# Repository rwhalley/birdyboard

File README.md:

# BirdyBoard 🦜

## What is BirdyBoard?

BirdyBoard is an open source Stepper Motor Controller Board powered by the Raspberry Pi Pico. BirdyBoard enables low-level control of stepper motors via the TMC2209 motor driver, making it possible to control the absolute position of gantry components without End Stop Switches. 

Create custom PCB modifications for creative projects with BirdyBoard.

## Creating Accessibility Despite Chip Shortages

BirdyBoard uses the RP2040 chip which is readily available even though the chip shortage (as of 2022) has rendered other chip options unavailable. The BirdyBoard allows for direct placement of the Pi Pico breakout board and TMC2209 breakout boards giving the reliability of a PCB without the need for complex or tedious soldering procedures for assembly.

## Link To Build of Materials + PCB Trace Tool Spreadsheets

https://docs.google.com/spreadsheets/d/1NhMLRXCss38mAH5ybtot6I5Q5R5pm-g04sVmaoJh7os/edit?usp=sharing

## Link to Pi Pico KiCad Layout Files

KiCad board layouts for the Raspberry Pi Pico are available here: https://github.com/ncarandini/KiCad-RP-Pico

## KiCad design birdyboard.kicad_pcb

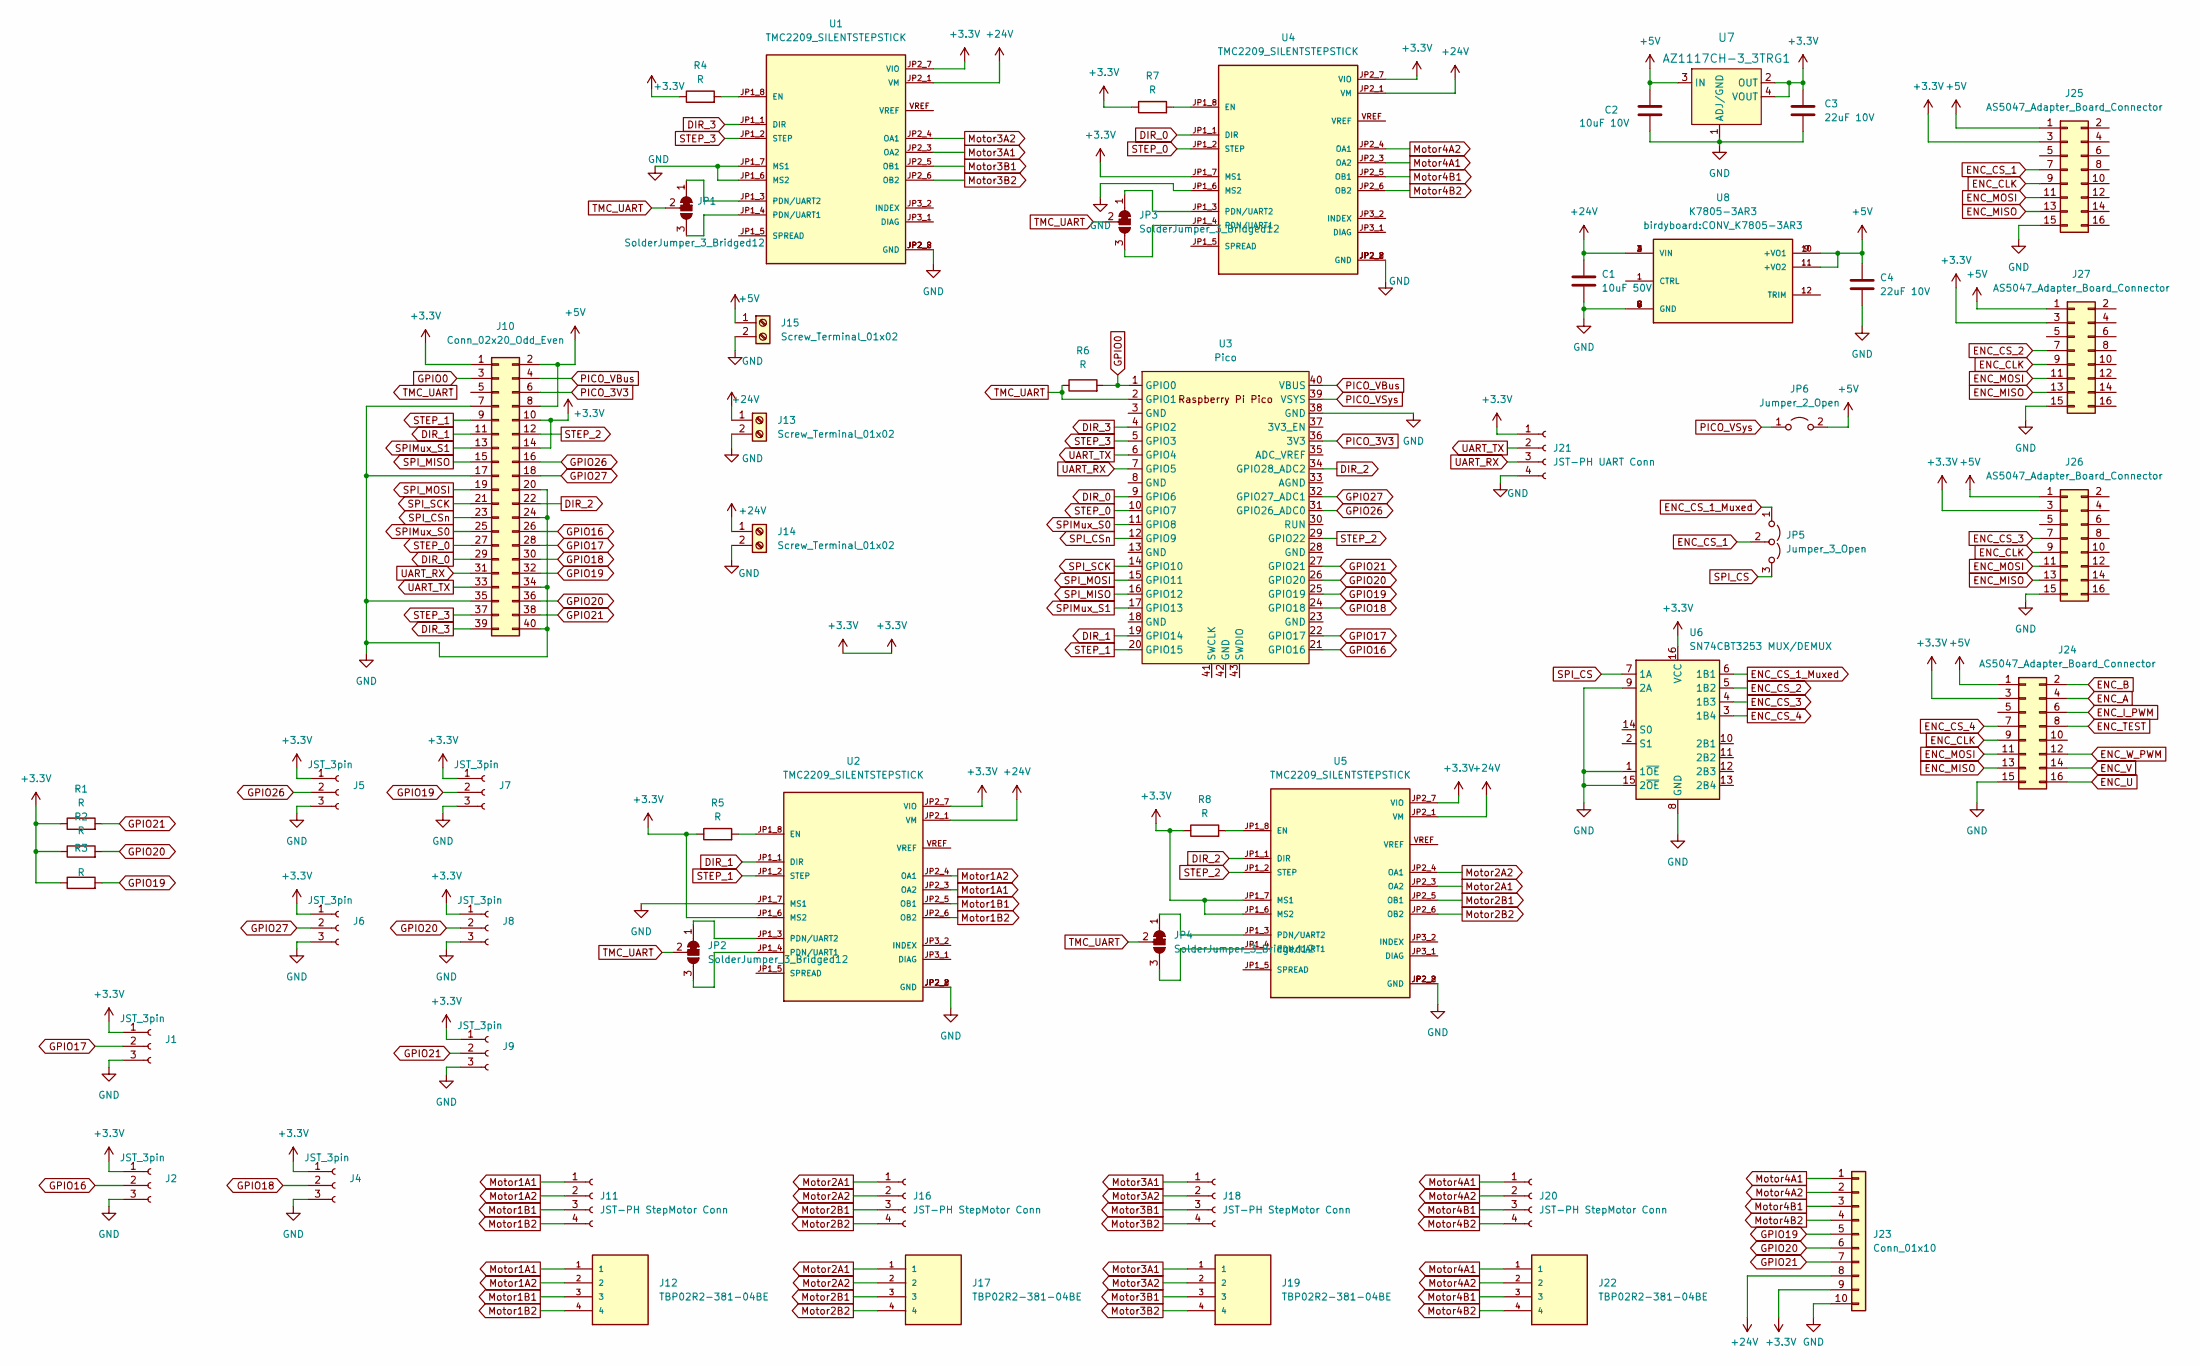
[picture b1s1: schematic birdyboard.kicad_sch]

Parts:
C1: 10uF 50V; C_0805_2012Metric_Pad1.18x1.45mm_HandSolder
C2: 10uF 10V; C_0805_2012Metric_Pad1.18x1.45mm_HandSolder
C3, C4: 22uF 10V; C_0805_2012Metric_Pad1.18x1.45mm_HandSolder
J1, J2, J4, J5, J6, J7, J8, J9: JST_3pin; JST_XH_B3B-XH-A_1x03_P2.50mm_Vertical
J10: Conn_02x20_Odd_Even; PinHeader_2x20_P2.54mm_Vertical_SMD
J11, J16, J18, J20: JST-PH StepMotor Conn; JST_XH_B4B-XH-A_1x04_P2.50mm_Vertical
J12, J17, J19, J22: TBP02R2-381-04BE; CUI_TBP02R2-381-04BE
J13, J14, J15: Screw_Terminal_01x02; CUI_TBP01R2-508-02BE
J21: JST-PH UART Conn; JST_XH_B4B-XH-A_1x04_P2.50mm_Vertical
J23: Conn_01x10
J24, J25, J26, J27: AS5047_Adapter_Board_Connector; PinHeader_2x08_P2.54mm_Vertical_SMD
JP1, JP2, JP3, JP4: SolderJumper_3_Bridged12; SolderJumper-3_P1.3mm_Bridged2Bar12_Pad1.0x1.5mm_NumberLabe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
JP5: Jumper_3_Open; SolderJumper-3_P1.3mm_Bridged2Bar12_Pad1.0x1.5mm_NumberLabe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
JP6: Jumper_2_Open; PinHeader_1x02_P2.54mm_Vertical
R1, R2, R3, R4, R5, R6, R7, R8: R; R_0805_2012Metric_Pad1.20x1.40mm_HandSolder
U1, U2, U4, U5: TMC2209_SILENTSTEPSTICK; TMC2208_SILENTSTEPSTICK
U3: Pico; RPi_Pico_SMD_TH
U6: SN74CBT3253 MUX/DEMUX; TSSOP-16_4.4x5mm_P0.65mm
U7: AZ1117CH-3_3TRG1; SOT-89-3; MPN AZ1117CH-3.3TRG1; Digi-Key_PN AZ1117CH-3.3TRG1DICT-ND
U8: K7805-3AR3; CONV_K7805-3AR3; PARTREV 2021.01.29-A/2

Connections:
+3.3V: C3.1, J1.1, J2.1, J4.1, J5.1, J6.1, J7.1, J8.1, J9.1, J10.1, J10.10, J10.14, J21.1, J23.9, J24.3, J25.3, J26.3, J27.3, R1.1, R2.1, R3.1, R4.1, R5.1, R7.1, R8.1, U1.JP2_7 (VIO), U2.JP1_6 (MS2), U2.JP2_7 (VIO), U4.JP1_7 (MS1), U4.JP2_7 (VIO), U5.JP1_6 (MS2), U5.JP1_7 (MS1), U5.JP2_7 (VIO), U6.16 (VCC), U7.2 (OUT), U7.4 (VOUT)
+5V: C2.1, C4.1, J10.2, J10.8, J15.1, J24.1, J25.1, J26.1, J27.1, JP6.2 (B), U7.3 (IN), U8.9 (+VO1), U8.10 (+VO1), U8.11 (+VO2)
+24V: C1.1, J13.1, J14.1, J23.8, U1.JP2_1 (VM), U2.JP2_1 (VM), U4.JP2_1 (VM), U5.JP2_1 (VM), U8.2 (VIN), U8.3 (VIN), U8.4 (VIN)
DIR_0: J10.29, U3.9 (GPIO6), U4.JP1_1 (DIR)
DIR_1: J10.11, U2.JP1_1 (DIR), U3.19 (GPIO14)
DIR_2: J10.22, U3.34 (GPIO28_ADC2), U5.JP1_1 (DIR)
DIR_3: J10.39, U1.JP1_1 (DIR), U3.4 (GPIO2)
ENC_A: J24.4
ENC_B: J24.2
ENC_CLK: J24.9, J25.9, J26.9, J27.9
ENC_CS_1: J25.7, JP5.2 (C)
ENC_CS_1_Muxed: JP5.1 (A), U6.6 (1B1)
ENC_CS_2: J27.7, U6.5 (1B2)
ENC_CS_3: J26.7, U6.4 (1B3)
ENC_CS_4: J24.7, U6.3 (1B4)
ENC_I_PWM: J24.6
ENC_MISO: J24.13, J25.13, J26.13, J27.13
ENC_MOSI: J24.11, J25.11, J26.11, J27.11
ENC_TEST: J24.8
ENC_U: J24.16
ENC_V: J24.14
ENC_W_PWM: J24.12
GND: C1.2, C2.2, C3.2, C4.2, J1.3, J2.3, J4.3, J5.3, J6.3, J7.3, J8.3, J9.3, J10.7, J10.17, J10.20, J10.24, J10.34, J10.35, J10.40, J13.2, J14.2, J15.2, J21.4, J23.10, J24.15, J25.15, J26.15, J27.15, U1.JP1_6 (MS2), U1.JP1_7 (MS1), U1.JP2_2 (GND), U1.JP2_8 (GND), U2.JP1_7 (MS1), U2.JP2_2 (GND), U2.JP2_8 (GND), U3.38 (GND), U4.JP1_6 (MS2), U4.JP2_2 (GND), U4.JP2_8 (GND), U5.JP2_2 (GND), U5.JP2_8 (GND), U6.1 (1~OE), U6.8 (GND), U6.9 (2A), U6.15 (2~OE), U7.1 (ADJ/GND), U8.5 (GND), U8.6 (GND), U8.7 (GND), U8.8 (GND)
GPIO0: J10.3, R6.2, U3.1 (GPIO0)
GPIO16: J2.2, J10.26, U3.21 (GPIO16)
GPIO17: J1.2, J10.28, U3.22 (GPIO17)
GPIO18: J4.2, J10.30, U3.24 (GPIO18)
GPIO19: J7.2, J10.32, J23.5, R3.2, U3.25 (GPIO19)
GPIO20: J8.2, J10.36, J23.6, R2.2, U3.26 (GPIO20)
GPIO21: J9.2, J10.38, J23.7, R1.2, U3.27 (GPIO21)
GPIO26: J5.2, J10.16, U3.31 (GPIO26_ADC0)
GPIO27: J6.2, J10.18, U3.32 (GPIO27_ADC1)
Motor1A1: J11.1, J12.1, U2.JP2_3 (OA2)
Motor1A2: J11.2, J12.2, U2.JP2_4 (OA1)
Motor1B1: J11.3, J12.3, U2.JP2_5 (OB1)
Motor1B2: J11.4, J12.4, U2.JP2_6 (OB2)
Motor2A1: J16.1, J17.1, U5.JP2_3 (OA2)
Motor2A2: J16.2, J17.2, U5.JP2_4 (OA1)
Motor2B1: J16.3, J17.3, U5.JP2_5 (OB1)
Motor2B2: J16.4, J17.4, U5.JP2_6 (OB2)
Motor3A1: J18.1, J19.1, U1.JP2_3 (OA2)
Motor3A2: J18.2, J19.2, U1.JP2_4 (OA1)
Motor3B1: J18.3, J19.3, U1.JP2_5 (OB1)
Motor3B2: J18.4, J19.4, U1.JP2_6 (OB2)
Motor4A1: J20.1, J22.1, J23.1, U4.JP2_3 (OA2)
Motor4A2: J20.2, J22.2, J23.2, U4.JP2_4 (OA1)
Motor4B1: J20.3, J22.3, J23.3, U4.JP2_5 (OB1)
Motor4B2: J20.4, J22.4, J23.4, U4.JP2_6 (OB2)
unnamed: JP1.1 (A), U1.JP1_3 (PDN/UART2)
unnamed: JP1.3 (B), U1.JP1_4 (PDN/UART1)
unnamed: JP2.1 (A), U2.JP1_3 (PDN/UART2)
unnamed: JP2.3 (B), U2.JP1_4 (PDN/UART1)
unnamed: JP3.1 (A), U4.JP1_3 (PDN/UART2)
unnamed: JP3.3 (B), U4.JP1_4 (PDN/UART1)
unnamed: JP4.1 (A), U5.JP1_3 (PDN/UART2)
unnamed: JP4.3 (B), U5.JP1_4 (PDN/UART1)
unnamed: R4.2, U1.JP1_8 (EN)
unnamed: R5.2, U2.JP1_8 (EN)
unnamed: R7.2, U4.JP1_8 (EN)
unnamed: R8.2, U5.JP1_8 (EN)
PICO_3V3: J10.6, U3.36 (3V3)
PICO_VBus: J10.4, U3.40 (VBUS)
PICO_VSys: JP6.1 (A), U3.39 (VSYS)
SPIMux_S0: J10.25, U3.11 (GPIO8)
SPIMux_S1: J10.13, U3.17 (GPIO13)
SPI_CS: JP5.3 (B), U6.7 (1A)
SPI_CSn: J10.23, U3.12 (GPIO9)
SPI_MISO: J10.15, U3.16 (GPIO12)
SPI_MOSI: J10.19, U3.15 (GPIO11)
SPI_SCK: J10.21, U3.14 (GPIO10)
STEP_0: J10.27, U3.10 (GPIO7), U4.JP1_2 (STEP)
STEP_1: J10.9, U2.JP1_2 (STEP), U3.20 (GPIO15)
STEP_2: J10.12, U3.29 (GPIO22), U5.JP1_2 (STEP)
STEP_3: J10.37, U1.JP1_2 (STEP), U3.5 (GPIO3)
TMC_UART: JP1.2 (C), JP2.2 (C), JP3.2 (C), JP4.2 (C), R6.1, U3.2 (GPIO1)
UART_RX: J10.31, J21.3, U3.7 (GPIO5)
UART_TX: J10.33, J21.2, U3.6 (GPIO4)

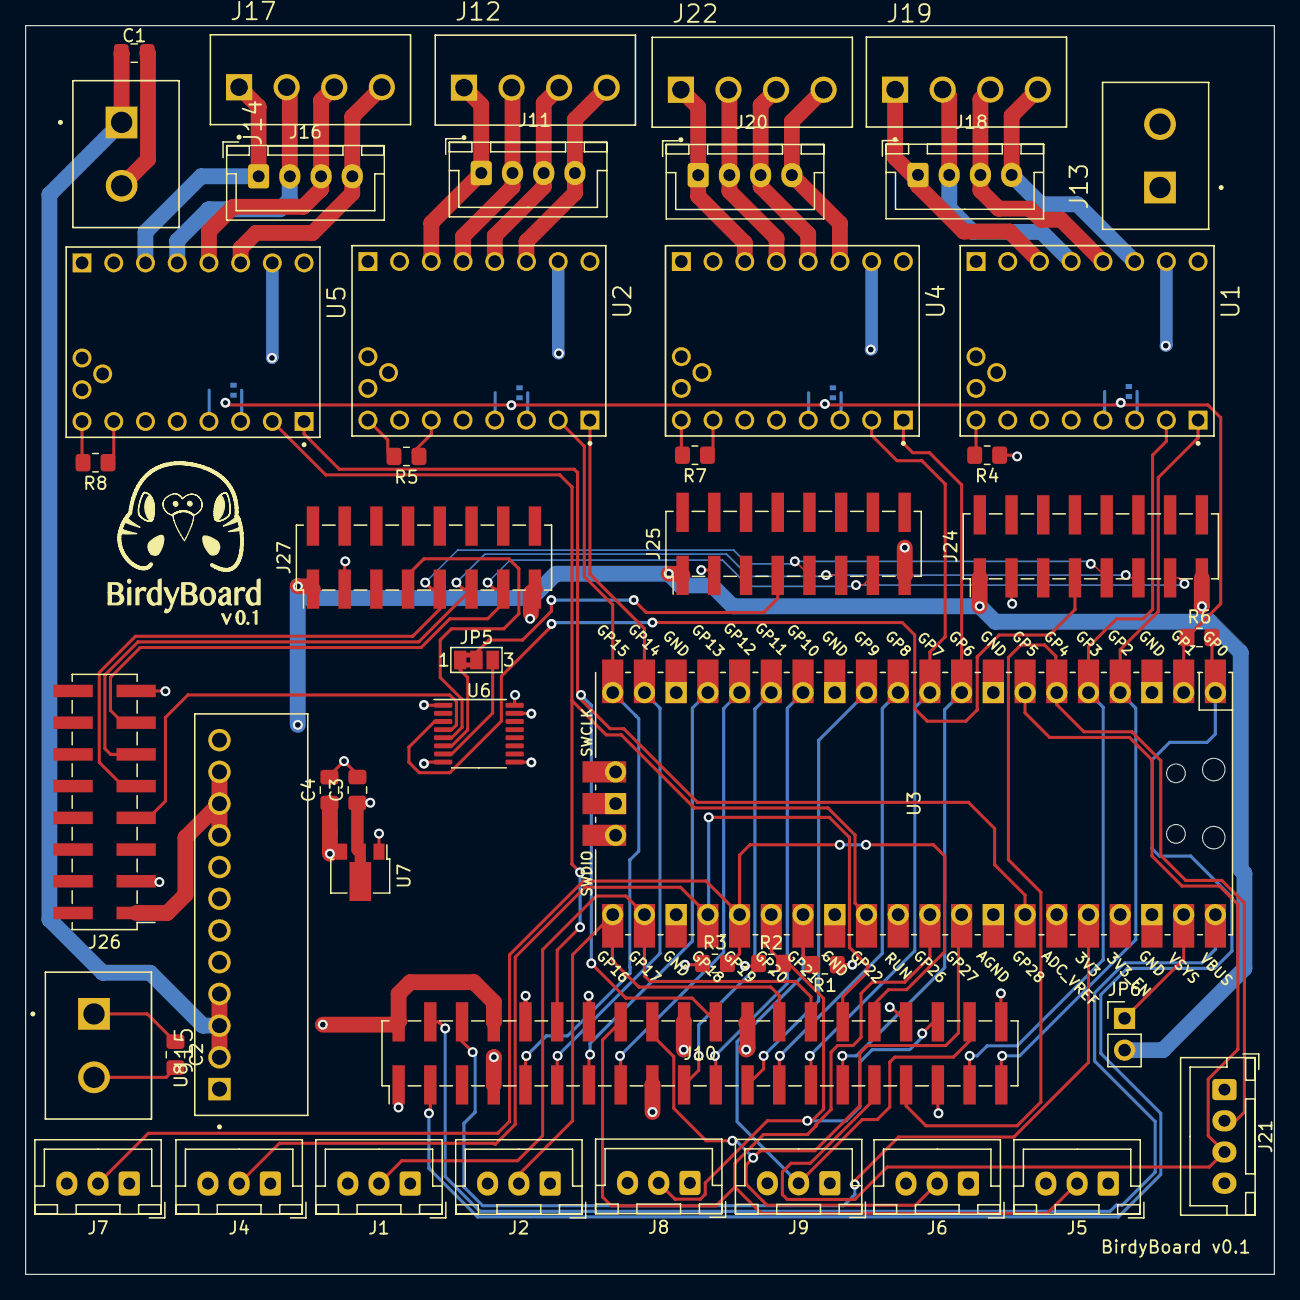
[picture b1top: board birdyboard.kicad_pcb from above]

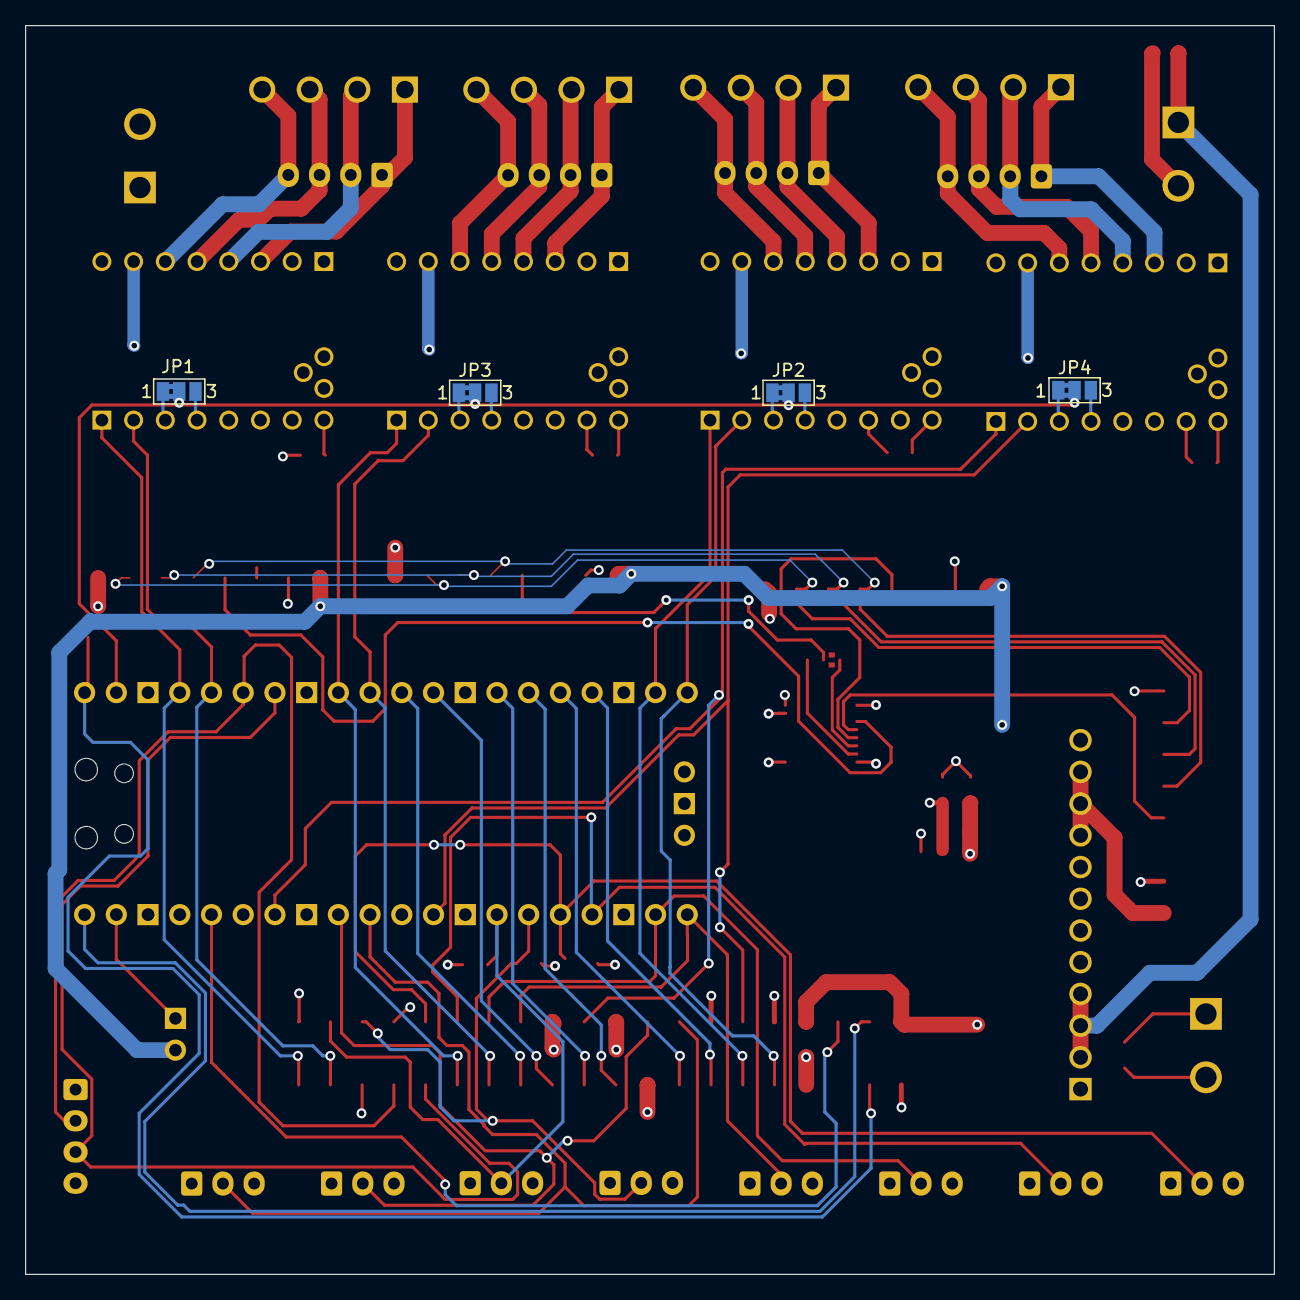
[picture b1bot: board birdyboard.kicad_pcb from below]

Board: 4 copper layers, 100.0 x 100.0 mm, 51 parts (4 on the bottom side), 70 nets.

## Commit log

2022-09-04 add basic content to readme
2022-09-04 add description of why birdyboard
2022-09-05 Adds footprints & symbols for RP2040 & TMC2208 boards
2022-09-06 Adds the main POWER terminals, adds a symbol and net names for AS5047 board header
2022-09-18 update schematic with new connections
2022-09-18 add netlabels and power ports
2022-09-18 fix small mistake
2022-09-18 add more netlabels
2022-09-18 small changes to schematic
2022-09-18 fix broken trace
2022-09-18 Adds 24-5v & 3.3v converters
    -- adds 3d model for TMC2209 stepsticks
    -- adds extra screw-terminal type connectors for stepper motors
    -- adds a jumper to allow a single encoder to run without installing a mux
    -- adds ENC_CS connections
2022-09-18 Completes TMC2209 & PSU circuits
2022-09-20 update power caps
2022-09-20 Update Schematic Labels
2022-09-20 Adds 40-pin header, cleans up stepper connections, add VIO connections for TMC, hooks up RP-PICO Power
2022-09-20 Adds 7 sensor inputs for limit switches and what not
2022-09-20 Adds pull ups to 3 sensor inputs, just for good measure
2022-09-28 Fixes most footprints and places footprints roughly at their final resting place
2022-10-04 -- Adds copper pours -- Adds netclasses & constraints for each netclasses -- Adds some pcb routes for some connections
2022-10-05 lay out some routes - place last components
2022-10-07 connects up the PCB Layout
2022-10-07 connect up last two power pads
2022-10-08 fix errors in DRC
2022-10-08 add Birdy logo
2022-10-08 improve logo resolution
2022-10-08 move logo
2022-10-17 update component
